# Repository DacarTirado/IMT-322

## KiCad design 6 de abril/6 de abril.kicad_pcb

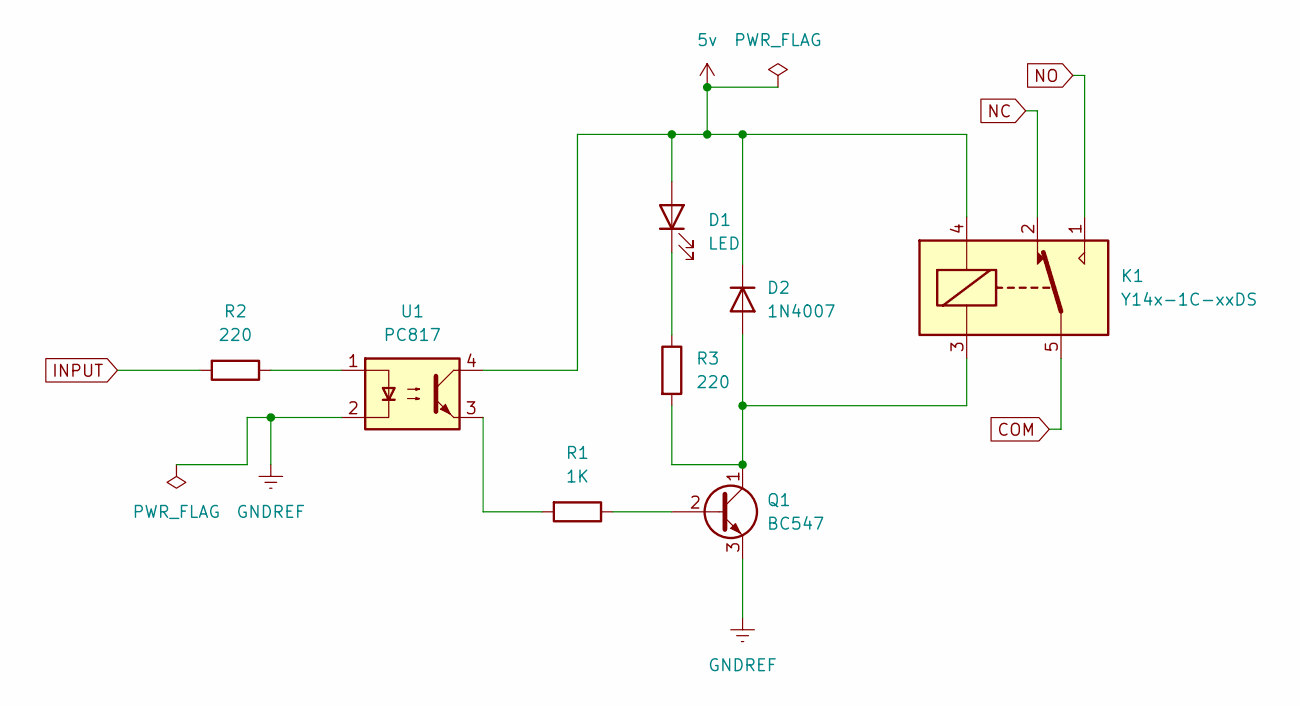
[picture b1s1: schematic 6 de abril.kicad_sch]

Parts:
D1: LED; LED_0805_2012Metric
D2: 1N4007; D_DO-41_SOD81_P10.16mm_Horizontal
K1: Y14x-1C-xxDS; Relay_SPDT_HsinDa_Y14
Q1: BC547; TO-92_Inline
R1: 1K; R_0805_2012Metric
R2, R3: 220; R_0805_2012Metric_Pad1.20x1.40mm_HandSolder
U1: PC817; DIP-4_W7.62mm

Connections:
5v: D1.2 (A), D2.1 (K), K1.4, U1.4
COM: K1.5, K1.6
GNDREF: Q1.3 (E), U1.2
INPUT: R2.2
NC: K1.2
NO: K1.1
unnamed: D1.1 (K), R3.1
unnamed: D2.2 (A), K1.3, Q1.1 (C), R3.2
unnamed: Q1.2 (B), R1.1
unnamed: R1.2, U1.3
unnamed: R2.1, U1.1

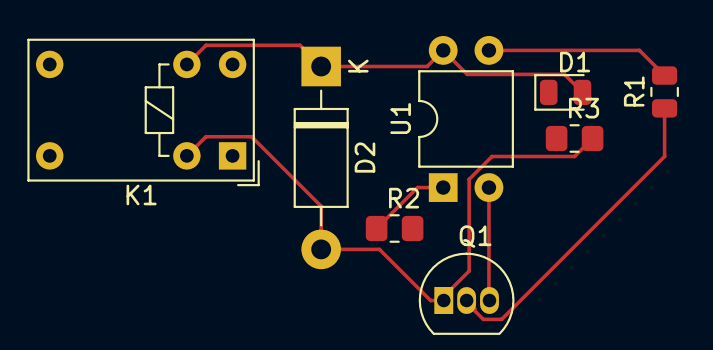
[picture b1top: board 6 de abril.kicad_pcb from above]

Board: 2 copper layers, 8 parts (0 on the bottom side), 8 nets.

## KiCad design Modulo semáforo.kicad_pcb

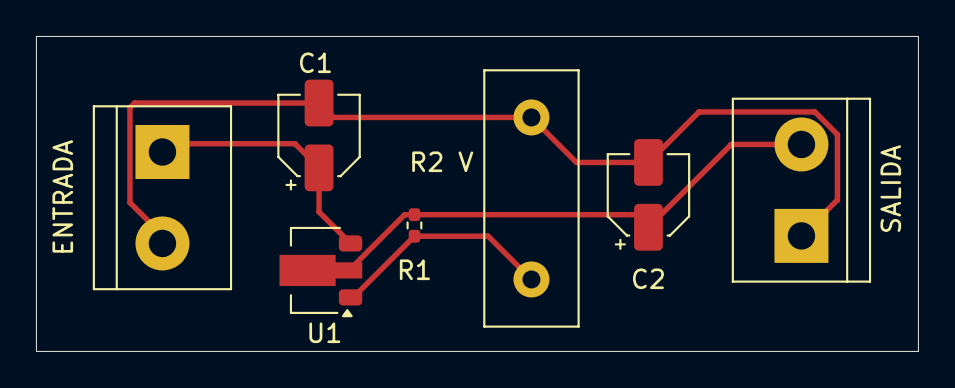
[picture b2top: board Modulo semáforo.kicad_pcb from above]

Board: 2 copper layers, 49.0 x 17.5 mm, 7 parts (0 on the bottom side), 4 nets.

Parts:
C1: 0.1uf; CP_Elec_4x3
C2: 47uf; CP_Elec_4x3
ENTRADA: TerminalBlock_bornier-2_P5.08mm
R1: 200; R_0402_1005Metric_Pad0.72x0.64mm_HandSolder
R2 V: 10K; R_Box_L14.0mm_W5.0mm_P9.00mm
SALIDA: TerminalBlock_bornier-2_P5.08mm
U1: LM317L_SOT-89; SOT-89-3

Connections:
GND: C1.2, C2.2, ENTRADA.2, R2 V.2, SALIDA.1
unnamed: R1.2, R2 V.1, U1.1 (ADJ)
VIN: C1.1, ENTRADA.1, U1.3 (VI)
VOUT: C2.1, R1.1, SALIDA.2, U1.2 (VO)

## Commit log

2024-02-17 DacarMeLaCome
2024-02-17 soygay
2024-04-13 nuevo
2024-04-21 sensor
2024-04-21 codigo semaforo
2024-04-22 placa impresa regulador
2024-04-22 placa pcb archivo correcto
2024-04-25 Ascensor
2024-04-27 EXAMEN 2
2024-04-30 Eamen 2 correjido
2024-05-21 Encendido Led Raspberry
2024-05-23 recuperatorio
2024-05-29 examen3
